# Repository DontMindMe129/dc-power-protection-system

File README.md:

# Hệ thống giám sát và bảo vệ đường nguồn DC

> Trạng thái: đang ở Giai đoạn 3 — Đặc tả thành phần. Đã có đủ bộ tài liệu spec sơ bộ, gồm Product Requirements, Design Spec, Hardware Spec v0.2, Software Spec v0.1 và Test Spec v0.1. Các thông số và điều kiện còn mở được theo dõi trong từng tài liệu để hoàn thiện khi thiết kế và chuẩn bị kiểm chứng.

Dự án nghiên cứu một thiết bị được mắc giữa nguồn DC bên ngoài và tải DC bên ngoài. Thiết bị giám sát trạng thái điện của đường công suất và có khả năng ngắt tải khi phát hiện điều kiện không an toàn.

Nhánh này được chủ ý giữ tối giản. Kiến trúc chức năng từ baseline v0.1 được giữ nguyên; cấu hình, quy tắc cảnh báo/ngắt và các mục tiêu hiệu năng được cập nhật theo Product Requirements v2. Miền điện áp 5–15 V đã được chọn; các chỉ tiêu hiệu năng còn lại vẫn là mục tiêu thiết kế, chưa phải kết quả đo. Phần cứng đang được khảo sát phương án; model linh kiện, schematic, PCB và firmware chưa được chốt. Tài liệu hiện tại là đầu vào cho đặc tả thành phần và thiết kế chi tiết, chưa chứng minh sản phẩm sẵn sàng chế tạo.

Tài liệu đang hoạt động:

- [`docs/concept.md`](docs/concept.md): phạm vi và cách hiểu hiện tại của dự án.
- [`docs/product-requirements.md`](docs/product-requirements.md): yêu cầu sản phẩm phiên bản 2, các tham số cấu hình, mục tiêu hiệu năng và phương pháp kiểm chứng dự kiến.
- [`docs/design-specification.md`](docs/design-specification.md): kiến trúc, trách nhiệm các khối, interface và hành vi giám sát/bảo vệ–phục hồi, được đồng bộ theo yêu cầu v2.
- [`docs/hardware-specification.md`](docs/hardware-specification.md): đặc tả phần cứng sơ bộ, các ngân sách đã chốt, hướng thiết kế và những mục cần hoàn thiện.
- [`docs/software-specification.md`](docs/software-specification.md): đặc tả firmware sơ bộ, tổ chức chức năng, đo lường, cấu hình, bảo vệ, trạng thái, UI, timing và kiểm chứng dự kiến.
- [`docs/test-specification.md`](docs/test-specification.md): đặc tả kiểm thử sơ bộ, bảng đối chiếu yêu cầu, phép thử từng khối/firmware/tích hợp, tiêu chí đạt và bản ghi bằng chứng.
- [`docs/diagrams/system-architecture.drawio`](docs/diagrams/system-architecture.drawio): bản vẽ gốc gồm bảy page (context, block diagram, bốn subsystem và state diagram); SVG tương ứng nằm trong `docs/diagrams/`.
- [`docs/development-process.md`](docs/development-process.md): quy trình phát triển và điều kiện chuyển giai đoạn theo môn học.

Phiên bản tài liệu được sinh trước đây vẫn được bảo tồn trên nhánh `main` và tag `archive/generated-v1`; chỉ dùng làm nguồn tham khảo, không phải thiết kế đã được chấp thuận.

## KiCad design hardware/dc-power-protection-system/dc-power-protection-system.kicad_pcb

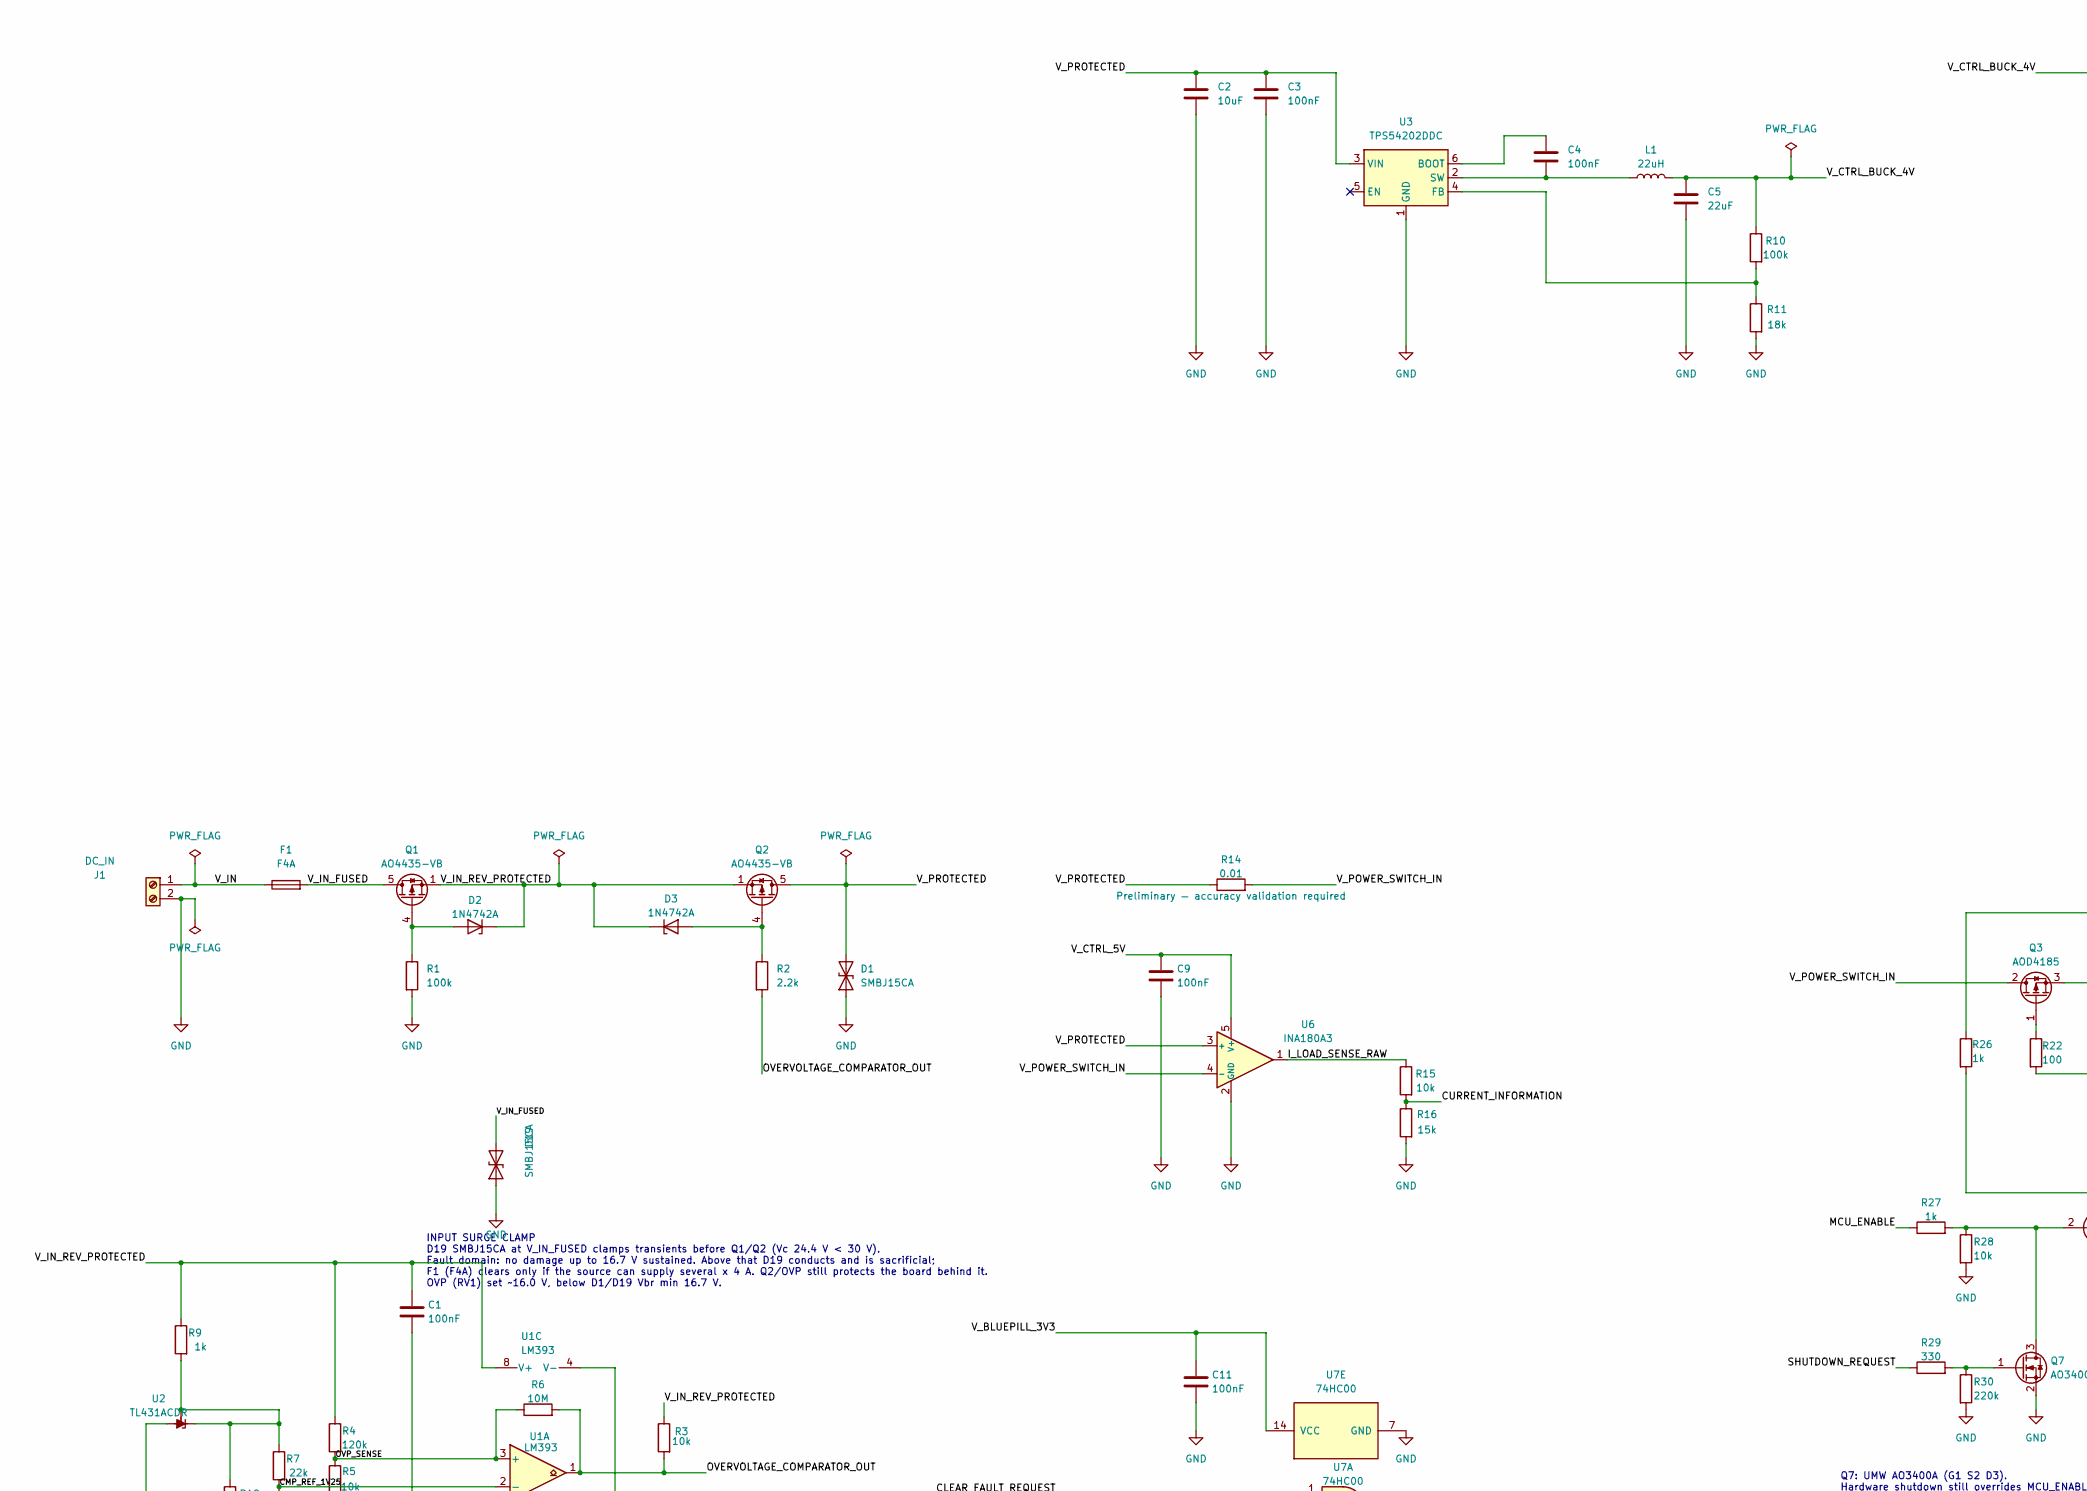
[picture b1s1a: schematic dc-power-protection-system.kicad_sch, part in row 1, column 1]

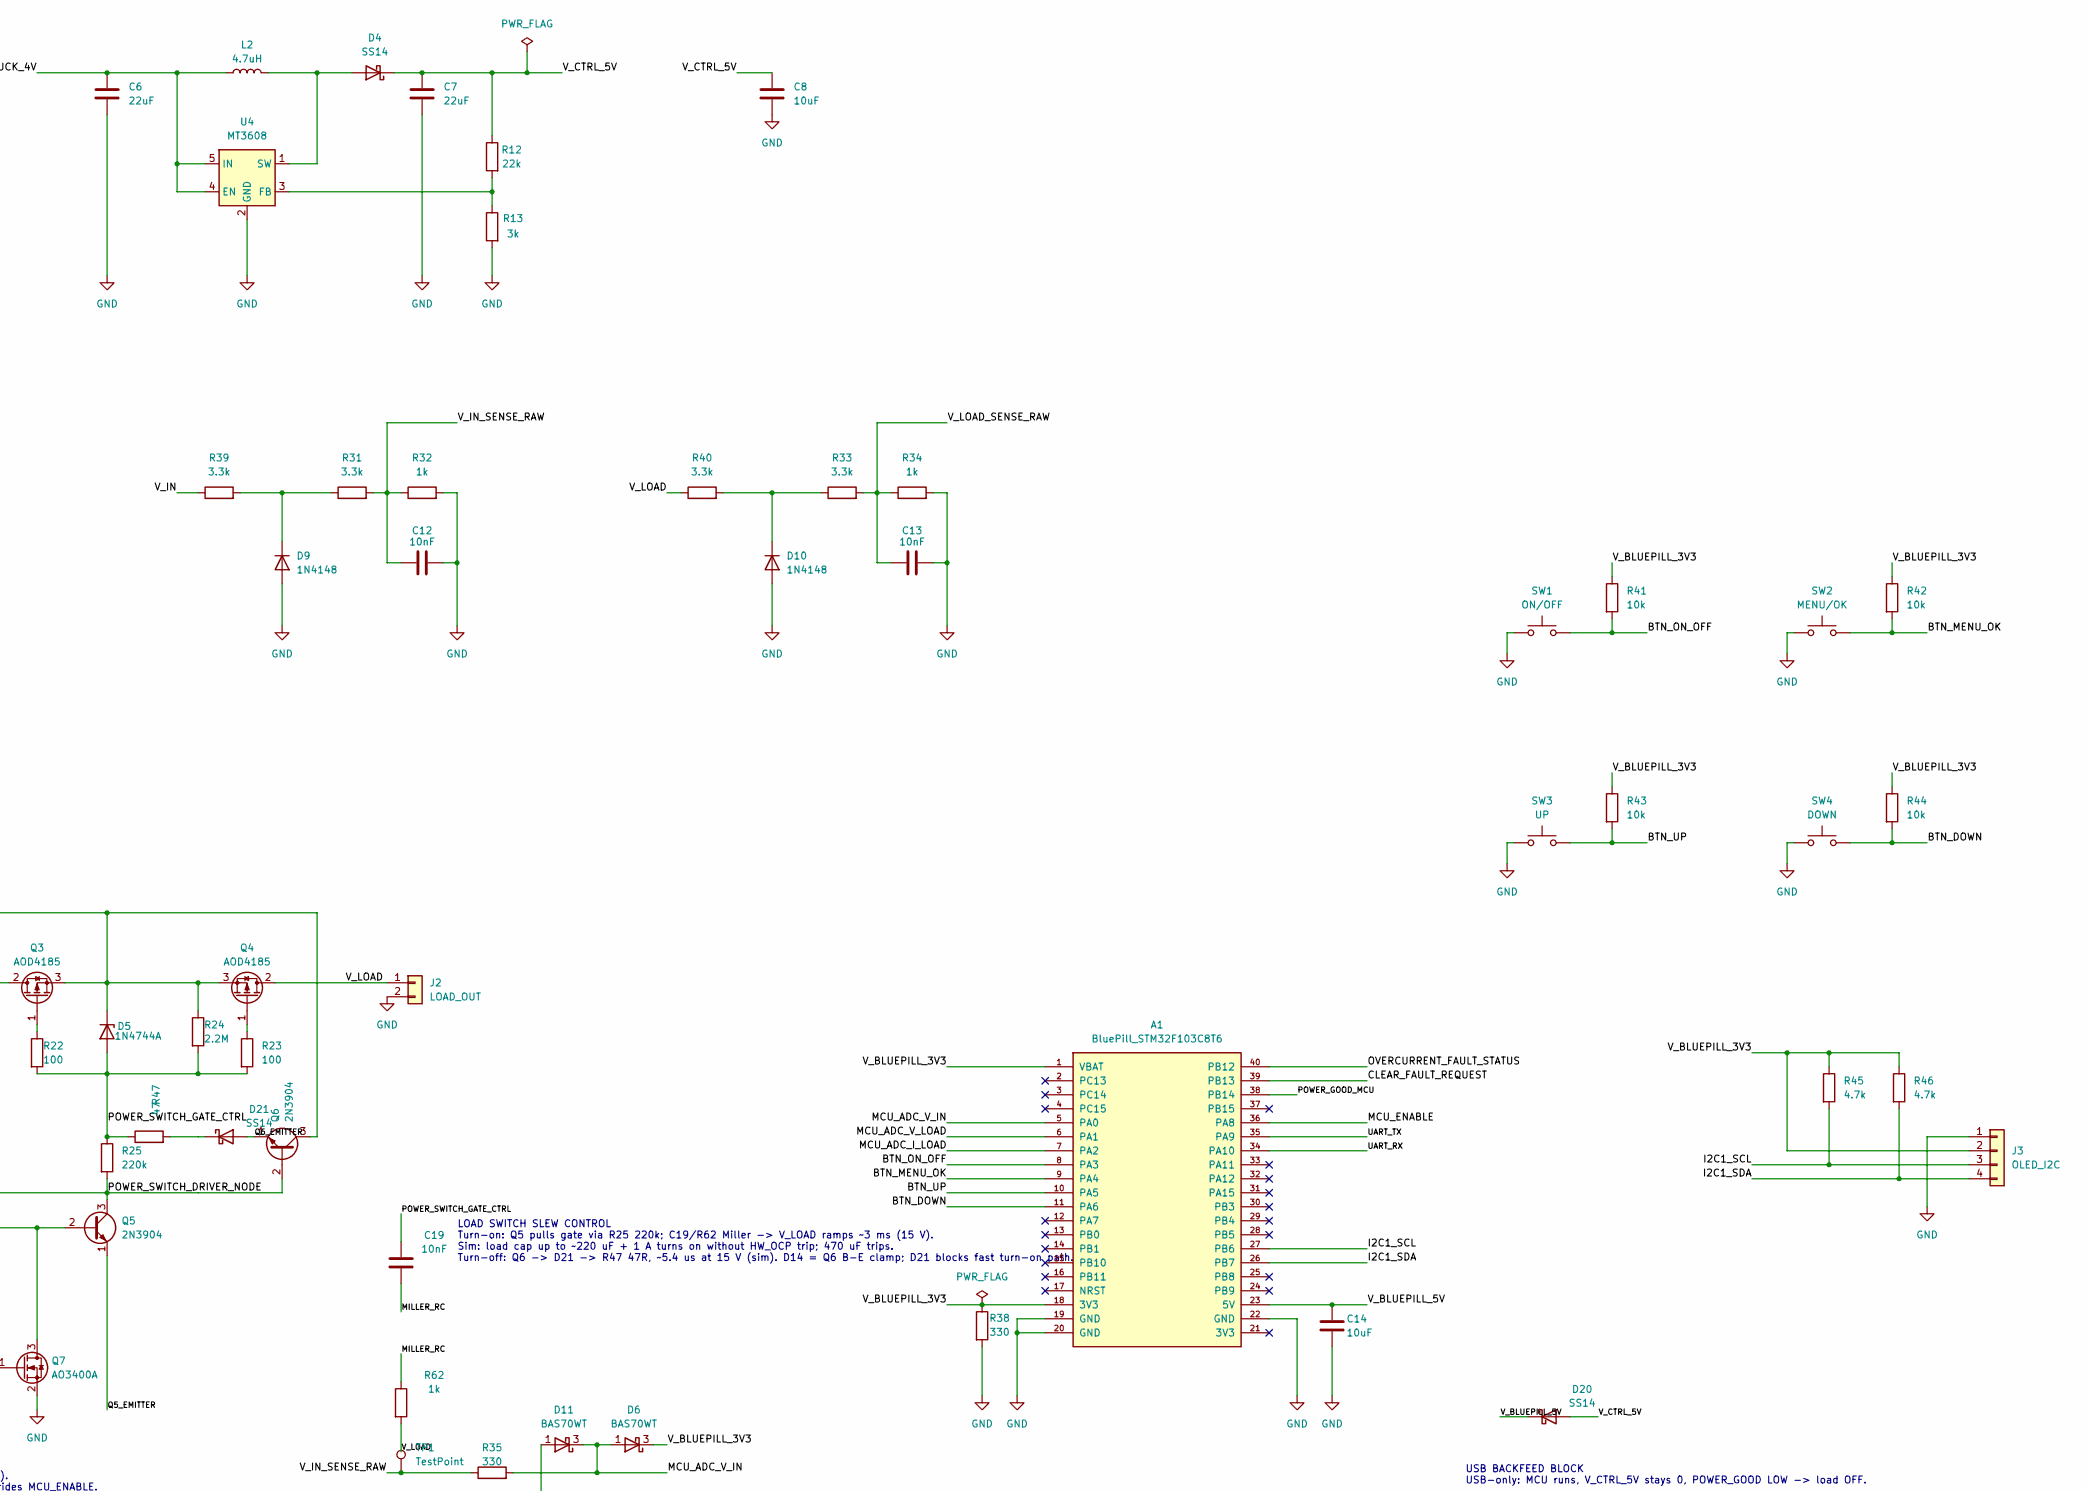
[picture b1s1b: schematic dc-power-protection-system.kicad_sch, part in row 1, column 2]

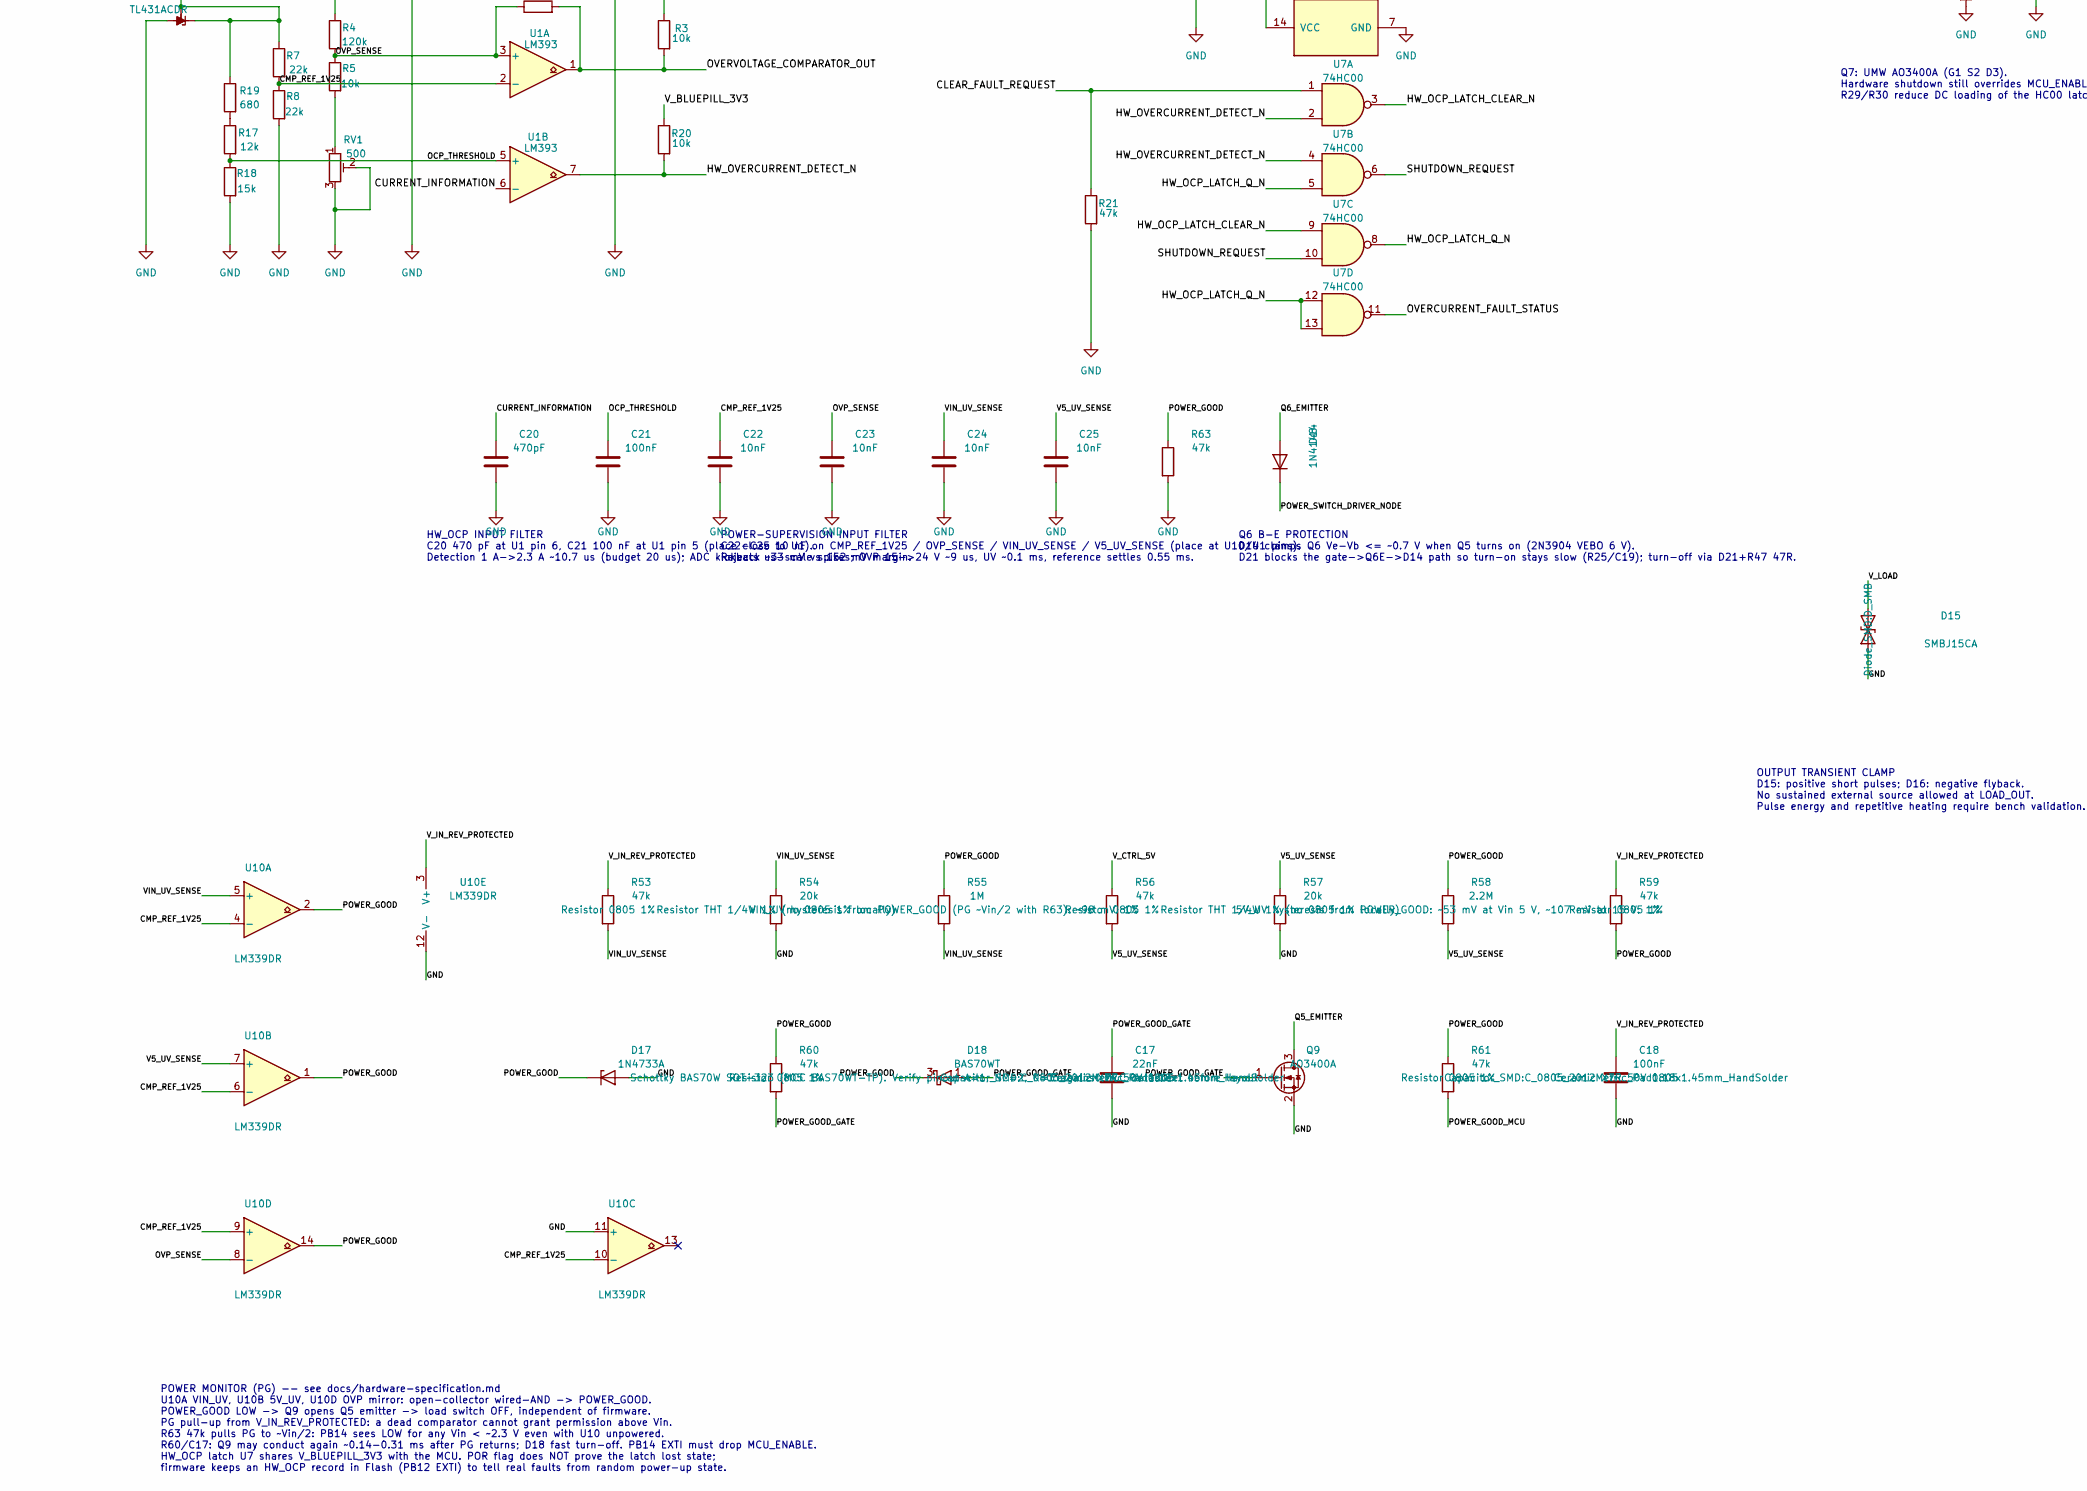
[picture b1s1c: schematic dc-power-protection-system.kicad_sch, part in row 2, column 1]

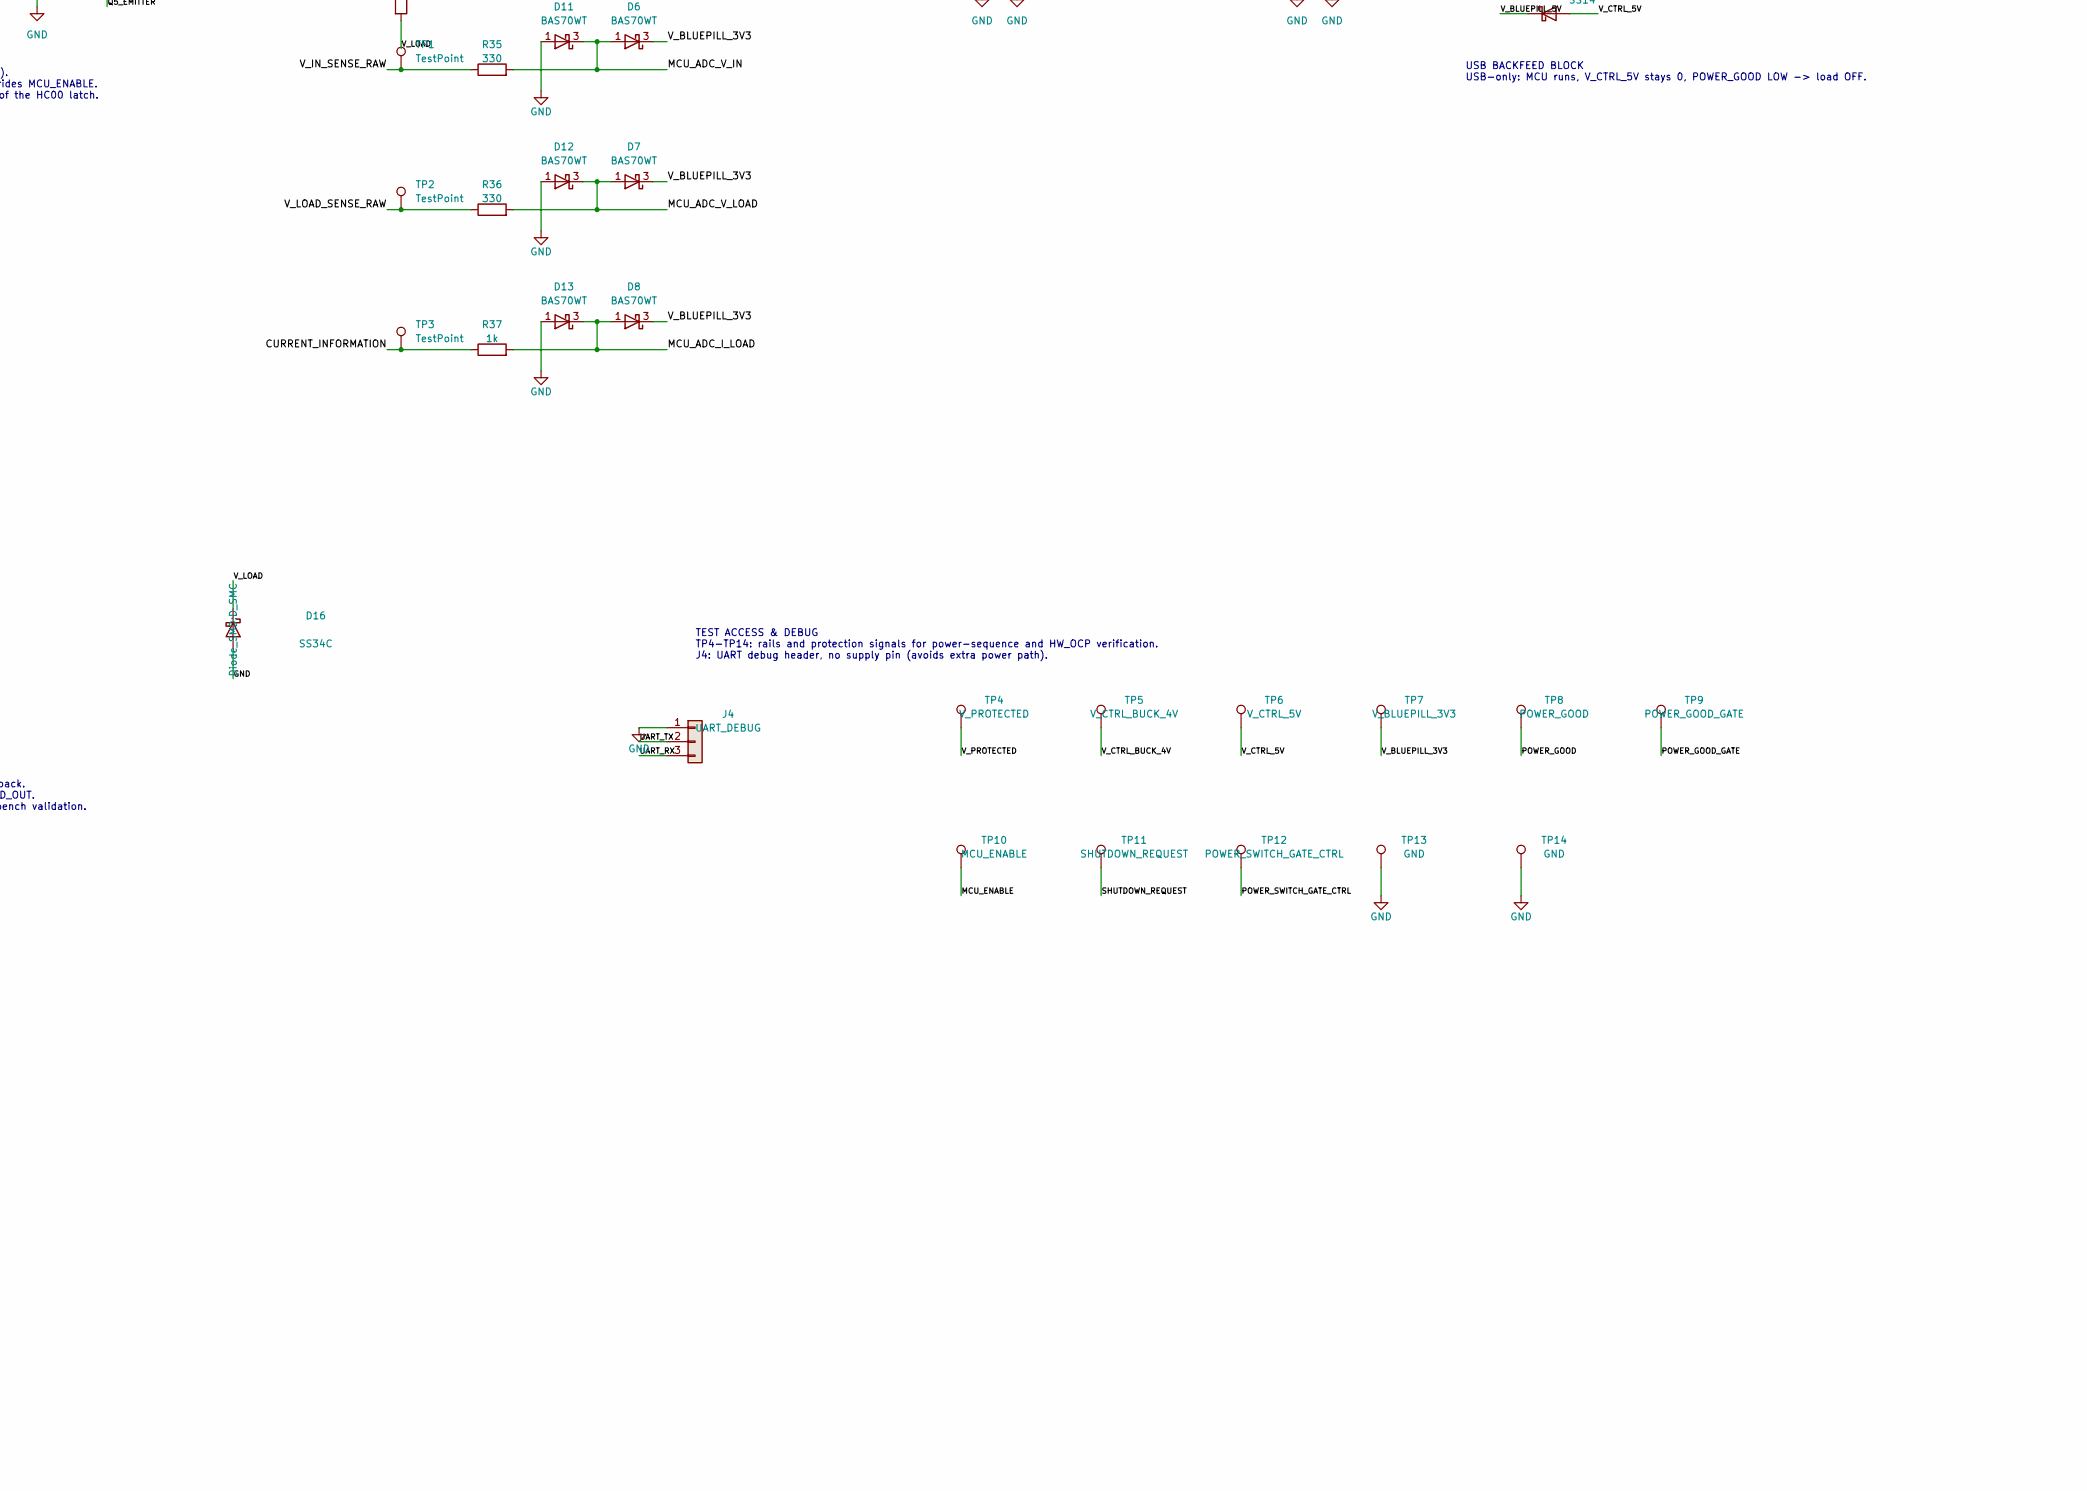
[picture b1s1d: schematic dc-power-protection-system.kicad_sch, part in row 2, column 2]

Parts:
A1: BluePill_STM32F103C8T6; DIP-40_W15.24mm_Socket_LongPads; MPN MKE-K06 STM32F103C8T6 Blue Pill
C1, C3, C4, C9, C11, C18, C21: 100nF; C_0805_2012Metric_Pad1.18x1.45mm_HandSolder; Voltage 50V; Tolerance 10%
C2: 10uF; C_1206_3216Metric_Pad1.33x1.80mm_HandSolder; Voltage 50V; Tolerance 10%
C5, C6, C7: 22uF; C_1206_3216Metric_Pad1.33x1.80mm_HandSolder; Voltage 16V; Tolerance 10%
C8, C14: 10uF; C_0805_2012Metric_Pad1.18x1.45mm_HandSolder; Voltage 50V; Tolerance 10%
C12, C13, C22, C23, C24, C25: 10nF; C_0805_2012Metric_Pad1.18x1.45mm_HandSolder; Voltage 50V; Tolerance 10%
C17: 22nF; C_0805_2012Metric_Pad1.18x1.45mm_HandSolder; Voltage 50V; Tolerance 10%
C19: 10nF; C_Rect_L7.2mm_W2.5mm_P5.00mm; Voltage 100V
C20: 470pF; C_0805_2012Metric_Pad1.18x1.45mm_HandSolder; Voltage 50V
D1, D15, D19: SMBJ15CA; D_SMB; MPN SMBJ15CA
D2, D3: 1N4742A; D_DO-41_SOD81_P10.16mm_Horizontal; Voltage 12V; MPN 1N4742A
D4, D20, D21: SS14; D_SMA; MPN SS14
D5: 1N4744A; D_DO-41_SOD81_P10.16mm_Horizontal; Voltage 15V; MPN 1N4744A
D6, D7, D8, D11, D12, D13, D18: BAS70WT; SOT-323_SC-70; MPN BAS70WT-TP
D9, D10, D14: 1N4148; D_DO-35_SOD27_P7.62mm_Horizontal; MPN 1N4148
D16: SS34C; D_SMC; MPN SS34 (SMC)
D17: 1N4733A; D_DO-41_SOD81_P10.16mm_Horizontal; Voltage 5.1V; MPN 1N4733A
F1: F4A; Fuseholder_Clip-5x20mm_Littelfuse_111_Inline_P20.00x5.00mm_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; MPN 5x20 mm glass fuse F4A 250V
J1: DC_IN; TerminalBlock_Phoenix_MKDS-1,5-2_1x02_P5.00mm_Horizontal; MPN KF301-2P 5.0 mm
J2: LOAD_OUT; TerminalBlock_Phoenix_MKDS-1,5-2_1x02_P5.00mm_Horizontal; MPN KF301-2P 5.0 mm
J3: OLED_I2C; PinSocket_1x04_P2.54mm_Vertical; MPN Female header 1x4 (cut from 1x20)
J4: UART_DEBUG; PinHeader_1x03_P2.54mm_Vertical
L1: 22uH; L_Changjiang_FXL0630; MPN 22uH molded 0630 (7x7x3 mm)
L2: 4.7uH; L_Changjiang_FXL0630; MPN 4.7uH molded 0630 (7x7x3 mm)
Q1, Q2: AO4435-VB; SOIC-8_3.9x4.9mm_P1.27mm; MPN AO4435-VB
Q3, Q4: AOD4185; TO-252-2; MPN AOD4185
Q5, Q6: 2N3904; TO-92_Inline; MPN 2N3904
Q7, Q9: AO3400A; SOT-23; MPN AO3400A (UMW)
R1, R10: 100k; R_0805_2012Metric_Pad1.20x1.40mm_HandSolder; Tolerance 1%
R2: 2.2k; R_0805_2012Metric_Pad1.20x1.40mm_HandSolder; Tolerance 1%
R3, R5, R15, R20, R28, R41, R42, R43, R44: 10k; R_0805_2012Metric_Pad1.20x1.40mm_HandSolder; Tolerance 1%
R4: 120k; R_0805_2012Metric_Pad1.20x1.40mm_HandSolder; Tolerance 1%
R6: 10M; R_Axial_DIN0207_L6.3mm_D2.5mm_P7.62mm_Horizontal; Tolerance 1%
R7, R8, R12: 22k; R_0805_2012Metric_Pad1.20x1.40mm_HandSolder; Tolerance 1%
R9: 1k; R_Axial_DIN0414_L11.9mm_D4.5mm_P15.24mm_Horizontal; Tolerance 1%
R11: 18k; R_0805_2012Metric_Pad1.20x1.40mm_HandSolder; Tolerance 1%
R13: 3k; R_Axial_DIN0207_L6.3mm_D2.5mm_P7.62mm_Horizontal; Tolerance 1%
R14: 0.01; R_2512_6332Metric_Pad1.40x3.35mm_HandSolder; Tolerance 1%
R16, R18: 15k; R_0805_2012Metric_Pad1.20x1.40mm_HandSolder; Tolerance 1%
R17: 12k; R_0805_2012Metric_Pad1.20x1.40mm_HandSolder; Tolerance 1%
R19: 680; R_0805_2012Metric_Pad1.20x1.40mm_HandSolder; Tolerance 1%
R21, R53, R56, R59, R60, R61, R63: 47k; R_0805_2012Metric_Pad1.20x1.40mm_HandSolder; Tolerance 1%
R22, R23: 100; R_0805_2012Metric_Pad1.20x1.40mm_HandSolder; Tolerance 1%
R24, R58: 2.2M; R_Axial_DIN0207_L6.3mm_D2.5mm_P7.62mm_Horizontal; Tolerance 1%
R25, R30: 220k; R_0805_2012Metric_Pad1.20x1.40mm_HandSolder; Tolerance 1%
R26: 1k; R_Axial_DIN0309_L9.0mm_D3.2mm_P12.70mm_Horizontal; Tolerance 5%
R27, R32, R34, R37, R62: 1k; R_0805_2012Metric_Pad1.20x1.40mm_HandSolder; Tolerance 1%
R29, R35, R36, R38: 330; R_0805_2012Metric_Pad1.20x1.40mm_HandSolder; Tolerance 5%
R31, R33, R39, R40: 3.3k; R_0805_2012Metric_Pad1.20x1.40mm_HandSolder; Tolerance 1%
R45, R46: 4.7k; R_0805_2012Metric_Pad1.20x1.40mm_HandSolder; Tolerance 1%
R47: 47; R_0805_2012Metric_Pad1.20x1.40mm_HandSolder; Tolerance 1%
R54, R57: 20k; R_Axial_DIN0207_L6.3mm_D2.5mm_P7.62mm_Horizontal; Tolerance 1%
R55: 1M; R_0805_2012Metric_Pad1.20x1.40mm_HandSolder; Tolerance 1%
RV1: 500; Potentiometer_Bourns_3296W_Vertical
SW1: ON/OFF; SW_SPST_PTS645Sx43SMTR92; MPN Tactile 6x6 mm H4.3 SMD 4-pin
SW2: MENU/OK; SW_SPST_PTS645Sx43SMTR92; MPN Tactile 6x6 mm H4.3 SMD 4-pin
SW3: UP; SW_SPST_PTS645Sx43SMTR92; MPN Tactile 6x6 mm H4.3 SMD 4-pin
SW4: DOWN; SW_SPST_PTS645Sx43SMTR92; MPN Tactile 6x6 mm H4.3 SMD 4-pin
TP1, TP2, TP3: TestPoint; TestPoint_THTPad_D2.0mm_Drill1.0mm
TP4: V_PROTECTED; TestPoint_THTPad_D2.0mm_Drill1.0mm
TP5: V_CTRL_BUCK_4V; TestPoint_THTPad_D2.0mm_Drill1.0mm
TP6: V_CTRL_5V; TestPoint_THTPad_D2.0mm_Drill1.0mm
TP7: V_BLUEPILL_3V3; TestPoint_THTPad_D2.0mm_Drill1.0mm
TP8: POWER_GOOD; TestPoint_THTPad_D2.0mm_Drill1.0mm
TP9: POWER_GOOD_GATE; TestPoint_THTPad_D2.0mm_Drill1.0mm
TP10: MCU_ENABLE; TestPoint_THTPad_D2.0mm_Drill1.0mm
TP11: SHUTDOWN_REQUEST; TestPoint_THTPad_D2.0mm_Drill1.0mm
TP12: POWER_SWITCH_GATE_CTRL; TestPoint_THTPad_D2.0mm_Drill1.0mm
TP13, TP14: GND; TestPoint_THTPad_D2.0mm_Drill1.0mm
U1: LM393; SOIC-8_3.9x4.9mm_P1.27mm; MPN LM393DR
U2: TL431ACDR; SOIC-8_3.9x4.9mm_P1.27mm; MPN TL431ACDR
U3: TPS54202DDC; SOT-23-6; MPN TPS54202DDCR
U4: MT3608; SOT-23-6; MPN MT3608
U6: INA180A3; SOT-23-5; MPN INA180A3IDBVR
U7: 74HC00; SOIC-14_3.9x8.7mm_P1.27mm; MPN 74HC00D
U10: LM339DR; SOIC-14_3.9x8.7mm_P1.27mm; MPN LM339DR

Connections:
/BTN_DOWN: A1.11 (PA6), R44.2, SW4.2
/BTN_MENU_OK: A1.9 (PA4), R42.2, SW2.2
/BTN_ON_OFF: A1.8 (PA3), R41.2, SW1.2
/BTN_UP: A1.10 (PA5), R43.2, SW3.2
/CLEAR_FAULT_REQUEST: A1.39 (PB13), R21.1, U7.1
/CMP_REF_1V25: C22.1, R7.2, R8.1, U1.2 (-), U10.4 (-), U10.6 (-), U10.9 (+), U10.10 (-)
/CURRENT_INFORMATION: C20.1, R15.2, R16.1, R37.1, TP3.1 (1_1), U1.6 (-)
/HW_OCP_LATCH_CLEAR_N: U7.3, U7.9
/HW_OCP_LATCH_Q_N: U7.5, U7.8, U7.12, U7.13
/HW_OVERCURRENT_DETECT_N: R20.2, U1.7, U7.2, U7.4
/I2C1_SCL: A1.27 (PB6), J3.3, R45.2
/I2C1_SDA: A1.26 (PB7), J3.4, R46.2
/I_LOAD_SENSE_RAW: R15.1, U6.1
/MCU_ADC_I_LOAD: A1.7 (PA2), D8.1 (A), D13.3 (K), R37.2
/MCU_ADC_V_IN: A1.5 (PA0), D6.1 (A), D11.3 (K), R35.2
/MCU_ADC_V_LOAD: A1.6 (PA1), D7.1 (A), D12.3 (K), R36.2
/MCU_ENABLE: A1.36 (PA8), R27.1, TP10.1 (1_1)
/MILLER_RC: C19.2, R62.1
/OCP_THRESHOLD: C21.1, R17.2, R18.1, U1.5 (+)
/OVERCURRENT_FAULT_STATUS: A1.40 (PB12), U7.11
/OVERVOLTAGE_COMPARATOR_OUT: R2.2, R3.2, R6.2, U1.1
/OVP_SENSE: C23.1, R4.2, R5.1, R6.1, U1.3 (+), U10.8 (-)
/POWER_GOOD: D17.1 (K), D18.3 (K), R55.1, R58.1, R59.2, R60.1, R61.1, R63.1, TP8.1 (1_1), U10.1, U10.2, U10.14
/POWER_GOOD_GATE: C17.1, D18.1 (A), Q9.1 (G), R60.2, TP9.1 (1_1)
/POWER_GOOD_MCU: A1.38 (PB14), R61.2
/POWER_SWITCH_DRIVER_NODE: D14.1 (K), Q5.3 (C), Q6.2 (B), R25.2, R26.2
/POWER_SWITCH_GATE_CTRL: C19.1, D5.2 (A), R22.2, R23.2, R24.2, R25.1, R47.1, TP12.1 (1_1)
/Q5_EMITTER: Q5.1 (E), Q9.3 (D)
/Q6_EMITTER: D14.2 (A), D21.2 (A), Q6.1 (E)
/SHUTDOWN_REQUEST: R29.1, TP11.1 (1_1), U7.6, U7.10
/UART_RX: A1.34 (PA10), J4.3
/UART_TX: A1.35 (PA9), J4.2
/V5_UV_SENSE: C25.1, R56.2, R57.1, R58.2, U10.7 (+)
/VIN_UV_SENSE: C24.1, R53.2, R54.1, R55.2, U10.5 (+)
/V_BLUEPILL_3V3: A1.1 (VBAT), A1.18 (3V3), C11.1, D6.3 (K), D7.3 (K), D8.3 (K), J3.2, R20.1, R38.1, R41.1, R42.1, R43.1, R44.1, R45.1, R46.1, TP7.1 (1_1), U7.14 (VCC)
/V_BLUEPILL_5V: A1.23 (5V), C14.1, D20.1 (K)
/V_CTRL_5V: C7.1, C8.1, C9.1, D4.1 (K), D20.2 (A), R12.1, R56.1, TP6.1 (1_1), U6.5 (V+)
/V_CTRL_BUCK_4V: C5.1, C6.1, L1.2, L2.1, R10.1, TP5.1 (1_1), U4.4 (EN), U4.5 (IN)
/V_IN: F1.1, J1.1, R39.1
/V_IN_FUSED: D19.2 (A2), F1.2, Q1.5 (D), Q1.6 (D), Q1.7 (D), Q1.8 (D)
/V_IN_REV_PROTECTED: C1.1, C18.1, D2.1 (K), D3.1 (K), Q1.1 (S), Q1.2 (S), Q1.3 (S), Q2.1 (S), Q2.2 (S), Q2.3 (S), R3.1, R4.1, R9.1, R53.1, R59.1, U1.8 (V+), U10.3 (V+)
/V_IN_SENSE_RAW: C12.1, R31.2, R32.1, R35.1, TP1.1 (1_1)
/V_LOAD: D15.2 (A2), D16.1 (K), J2.1, Q4.2 (D), R40.1, R62.2
/V_LOAD_SENSE_RAW: C13.1, R33.2, R34.1, R36.1, TP2.1 (1_1)
/V_POWER_SWITCH_IN: Q3.2 (D), R14.2, U6.4 (-)
/V_PROTECTED: C2.1, C3.1, D1.2 (A2), Q2.5 (D), Q2.6 (D), Q2.7 (D), Q2.8 (D), R14.1, TP4.1 (1_1), U3.3 (VIN), U6.3 (+)
GND: A1.19 (GND), A1.20 (GND), A1.22 (GND), C1.2, C2.2, C3.2, C5.2, C6.2, C7.2, C8.2, C9.2, C11.2, C12.2, C13.2, C14.2, C17.2, C18.2, C20.2, C21.2, C22.2, C23.2, C24.2, C25.2, D1.1 (A1), D9.2 (A), D10.2 (A), D11.1 (A), D12.1 (A), D13.1 (A), D15.1 (A1), D16.2 (A), D17.2 (A), D19.1 (A1), J1.2, J2.2, J3.1, J4.1, Q7.2 (S), Q9.2 (S), R1.2, R8.2, R11.2, R13.2, R16.2, R18.2, R21.2, R28.2, R30.2, R32.2, R34.2, R38.2, R54.2, R57.2, R63.2, RV1.2, RV1.3, SW1.1, SW2.1, SW3.1, SW4.1, TP13.1 (1_1), TP14.1 (1_1), U1.4 (V-), U2.2 (A), U2.3 (A), U2.6 (A), U2.7 (A), U3.1 (GND), U4.2 (GND), U6.2 (GND), U7.7 (GND), U10.11 (+), U10.12 (V-)
unnamed: D2.2 (A), Q1.4 (G), R1.1
unnamed: D3.2 (A), Q2.4 (G), R2.1
unnamed: D4.2 (A), L2.2, U4.1 (SW)
unnamed: D5.1 (K), Q3.3 (S), Q4.3 (S), Q6.3 (C), R24.1, R26.1
unnamed: D9.1 (K), R31.1, R39.2
unnamed: D10.1 (K), R33.1, R40.2
unnamed: D21.1 (K), R47.2
unnamed: Q3.1 (G), R22.1
unnamed: Q4.1 (G), R23.1
unnamed: Q5.2 (B), Q7.3 (D), R27.2, R28.1
unnamed: Q7.1 (G), R29.2, R30.1
unnamed: R5.2, RV1.1
unnamed: R17.1, R19.2
unnamed: R7.1, R9.2, R19.1, U2.1 (K), U2.8 (REF)
unnamed: C4.1, U3.6 (BOOT)
unnamed: R10.2, R11.1, U3.4 (FB)
unnamed: C4.2, L1.1, U3.2 (SW)
unnamed: R12.2, R13.1, U4.3 (FB)

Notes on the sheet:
OUTPUT TRANSIENT CLAMP D15: positive short pulses; D16: negative flyback. No sustained external source allowed at LOAD_OUT. Pulse energy and repetitive heating require bench validation.
POWER MONITOR (PG) -- see docs/hardware-specification.md U10A VIN_UV, U10B 5V_UV, U10D OVP mirror: open-collector wired-AND -> POWER_GOOD. POWER_GOOD LOW -> Q9 opens Q5 emitter -> load switch OFF, independent of firmware. PG pull-up from V_IN_REV_PROTECTED: a dead comparator cannot grant permission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
Q7: UMW AO3400A (G1 S2 D3). Hardware shutdown still overrides MCU_ENABLE. R29/R30 reduce DC loading of the HC00 latch.
INPUT SURGE CLAMP D19 SMBJ15CA at V_IN_FUSED clamps transients before Q1/Q2 (Vc 24.4 V < 30 V). Fault domain: no damage up to 16.7 V sustained. Above that D19 conducts and is sacrificial; F1 (F4A) clears only if the source can supply several x 4 A. Q2/OVP still protects the board behind it. OVP (RV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
USB BACKFEED BLOCK USB-only: MCU runs, V_CTRL_5V stays 0, POWER_GOOD LOW -> load OFF.
TEST ACCESS & DEBUG TP4-TP14: rails and protection signals for power-sequence and HW_OCP verification. J4: UART debug header, no supply pin (avoids extra power path).
LOAD SWITCH SLEW CONTROL Turn-on: Q5 pulls gate via R25 220k; C19/R62 Miller -> V_LOAD ramps ~3 ms (15 V). Sim: load cap up to ~220 uF + 1 A turns on without HW_OCP trip; 470 uF trips. Turn-off: Q6 -> D21 -> R47 47R, ~5.4 us at 15 V (sim). D14 = Q6 B-E clamp; D21 blocks fast turn-on path.
HW_OCP INPUT FILTER C20 470 pF at U1 pin 6, C21 100 nF at U1 pin 5 (place close to U1). Detection 1 A->2.3 A ~10.7 us (budget 20 us); ADC kickback ~33 mV vs 152 mV margin.
POWER-SUPERVISION INPUT FILTER C22-C25 10 nF on CMP_REF_1V25 / OVP_SENSE / VIN_UV_SENSE / V5_UV_SENSE (place at U10/U1 pins). Rejects us-scale spikes; OVP 15->24 V ~9 us, UV ~0.1 ms, reference settles 0.55 ms.
Q6 B-E PROTECTION D14 clamps Q6 Ve-Vb <= ~0.7 V when Q5 turns on (2N3904 VEBO 6 V). D21 blocks the gate->Q6E->D14 path so turn-on stays slow (R25/C19); turn-off via D21+R47 47R.
